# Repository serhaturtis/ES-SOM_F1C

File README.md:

<div id="top"></div>

<br />
<div align="center">

<h3 align="center">SOM-F1C</h3>

  <p align="center">
    A System-on-Module With Allwinner F1C Processor 
  </p>
</div>

<!-- WHAT -->
## What?

This is a linux capable system-on-module board made with Allwinner F1C processor. It can hold SPI flash memory (like 16MB NOR or 128MB NAND) on board. 

## Why?

Because I wanted to.

## How?

Headers are placed to the egdes so that manufacturer can recognize it for edge plating.

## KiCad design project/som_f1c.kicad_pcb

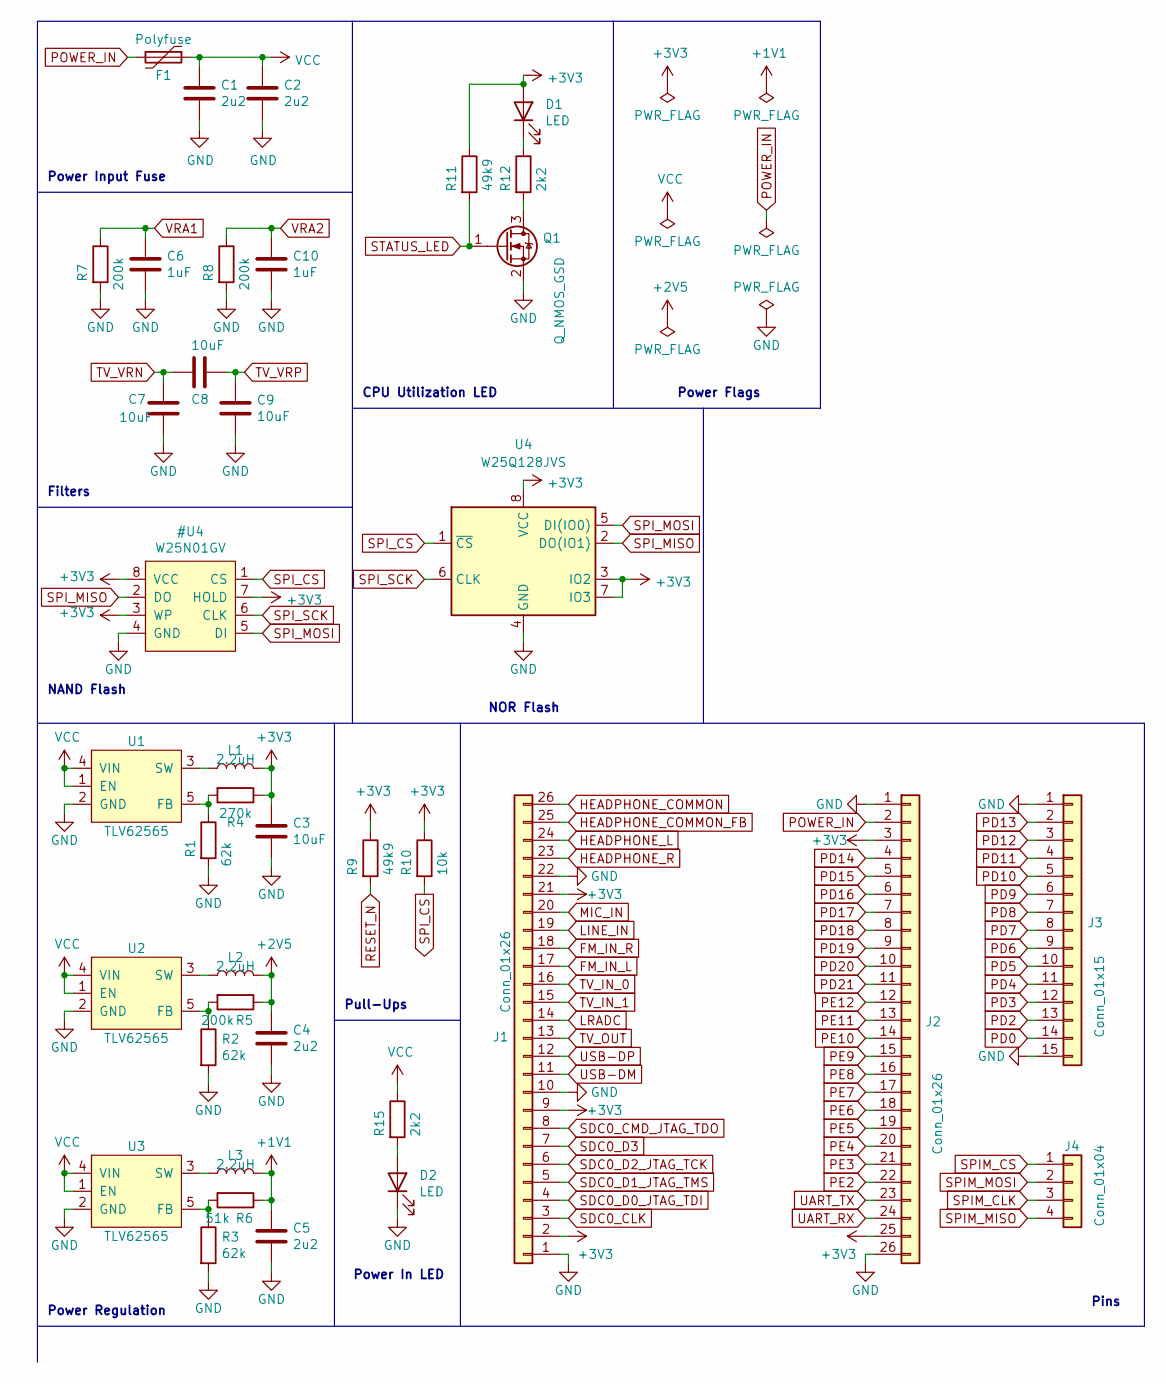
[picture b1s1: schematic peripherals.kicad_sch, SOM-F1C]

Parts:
C1, C2, C4, C5: 2u2; C_0402_1005Metric
C3, C7, C8, C9: 10uF; C_0402_1005Metric
C6, C10: 1uF; C_0402_1005Metric
D1, D2: LED; LED_0402_1005Metric
F1: Polyfuse; Fuse_1206_3216Metric
J1, J2: Conn_01x26; PinHeader_1x26_P1.27mm_Vertical
J3: Conn_01x15; PinHeader_1x15_P1.27mm_Vertical
J4: Conn_01x04; PinHeader_1x04_P1.27mm_Vertical
L1, L2, L3: 2.2uH; L_0805_2012Metric
Q1: Q_NMOS_GSD; SOT-323_SC-70
R1, R2, R3: 62k; R_0402_1005Metric
R4: 270k; R_0402_1005Metric
R5, R7, R8: 200k; R_0402_1005Metric
R6: 51k; R_0402_1005Metric
R9, R11: 49k9; R_0402_1005Metric
R10: 10k; R_0402_1005Metric
R12, R15: 2k2; R_0402_1005Metric
U1, U2, U3: TLV62565; SOT-23-5
U4: W25Q128JVS; SOIC-8_5.23x5.23mm_P1.27mm

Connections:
+1V1: C5.1, L3.2, R6.1; also elsewhere on the board
+2V5: C4.1, L2.2, R5.1; also elsewhere on the board
FM_IN_L: J1.17; also elsewhere on the board
FM_IN_R: J1.18; also elsewhere on the board
HEADPHONE_COMMON: J1.26; also elsewhere on the board
HEADPHONE_COMMON_FB: J1.25; also elsewhere on the board
HEADPHONE_L: J1.24; also elsewhere on the board
HEADPHONE_R: J1.23; also elsewhere on the board
LINE_IN: J1.19; also elsewhere on the board
LRADC: J1.14; also elsewhere on the board
MIC_IN: J1.20; also elsewhere on the board
unnamed: D1.1 (K), R12.1
unnamed: D2.2 (A), R15.2
unnamed: L1.1, U1.3 (SW)
unnamed: L2.1, U2.3 (SW)
unnamed: L3.1, U3.3 (SW)
unnamed: Q1.3 (D), R12.2
unnamed: R1.1, R4.2, U1.5 (FB)
unnamed: R2.1, R5.2, U2.5 (FB)
unnamed: R3.1, R6.2, U3.5 (FB)
PD0: J3.14; also elsewhere on the board
PD2: J3.13; also elsewhere on the board
PD3: J3.12; also elsewhere on the board
PD4: J3.11; also elsewhere on the board
PD5: J3.10; also elsewhere on the board
PD6: J3.9; also elsewhere on the board
PD7: J3.8; also elsewhere on the board
PD8: J3.7; also elsewhere on the board
PD9: J3.6; also elsewhere on the board
PD10: J3.5; also elsewhere on the board
PD11: J3.4; also elsewhere on the board
PD12: J3.3; also elsewhere on the board
PD13: J3.2; also elsewhere on the board
PD14: J2.4; also elsewhere on the board
PD15: J2.5; also elsewhere on the board
PD16: J2.6; also elsewhere on the board
PD17: J2.7; also elsewhere on the board
PD18: J2.8; also elsewhere on the board
PD19: J2.9; also elsewhere on the board
PD20: J2.10; also elsewhere on the board
PD21: J2.11; also elsewhere on the board
PE2: J2.22; also elsewhere on the board
PE3: J2.21; also elsewhere on the board
PE4: J2.20; also elsewhere on the board
PE5: J2.19; also elsewhere on the board
PE6: J2.18; also elsewhere on the board
PE7: J2.17; also elsewhere on the board
PE8: J2.16; also elsewhere on the board
PE9: J2.15; also elsewhere on the board
PE10: J2.14; also elsewhere on the board
PE11: J2.13; also elsewhere on the board
PE12: J2.12; also elsewhere on the board
POWER_IN: F1.2, J2.2
RESET_N: R9.2; also elsewhere on the board
SDC0_CLK: J1.3; also elsewhere on the board
SDC0_CMD_JTAG_TDO: J1.8; also elsewhere on the board
SDC0_D0_JTAG_TDI: J1.4; also elsewhere on the board
SDC0_D1_JTAG_TMS: J1.5; also elsewhere on the board
SDC0_D2_JTAG_TCK: J1.6; also elsewhere on the board
SDC0_D3: J1.7; also elsewhere on the board
SPIM_CLK: J4.3; also elsewhere on the board
SPIM_CS: J4.1; also elsewhere on the board
SPIM_MISO: J4.4; also elsewhere on the board
SPIM_MOSI: J4.2; also elsewhere on the board
STATUS_LED: Q1.1 (G), R11.2; also elsewhere on the board
TV_IN_0: J1.16; also elsewhere on the board
TV_IN_1: J1.15; also elsewhere on the board
TV_OUT: J1.13; also elsewhere on the board
TV_VRN: C7.1, C8.2; also elsewhere on the board
TV_VRP: C8.1, C9.1; also elsewhere on the board
UART_RX: J2.24; also elsewhere on the board
UART_TX: J2.23; also elsewhere on the board
USB-DM: J1.11; also elsewhere on the board
USB-DP: J1.12; also elsewhere on the board
VCC: C1.1, C2.1, F1.1, R15.1, U1.1 (EN), U1.4 (VIN), U2.1 (EN), U2.4 (VIN), U3.1 (EN), U3.4 (VIN)
VRA1: C6.1, R7.1; also elsewhere on the board
VRA2: C10.1, R8.1; also elsewhere on the board

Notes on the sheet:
NOR Flash
Pull-Ups
CPU Utilization LED
Power Regulation
Power Flags
NAND Flash
Pins
Power Input Fuse
Filters
Power In LED

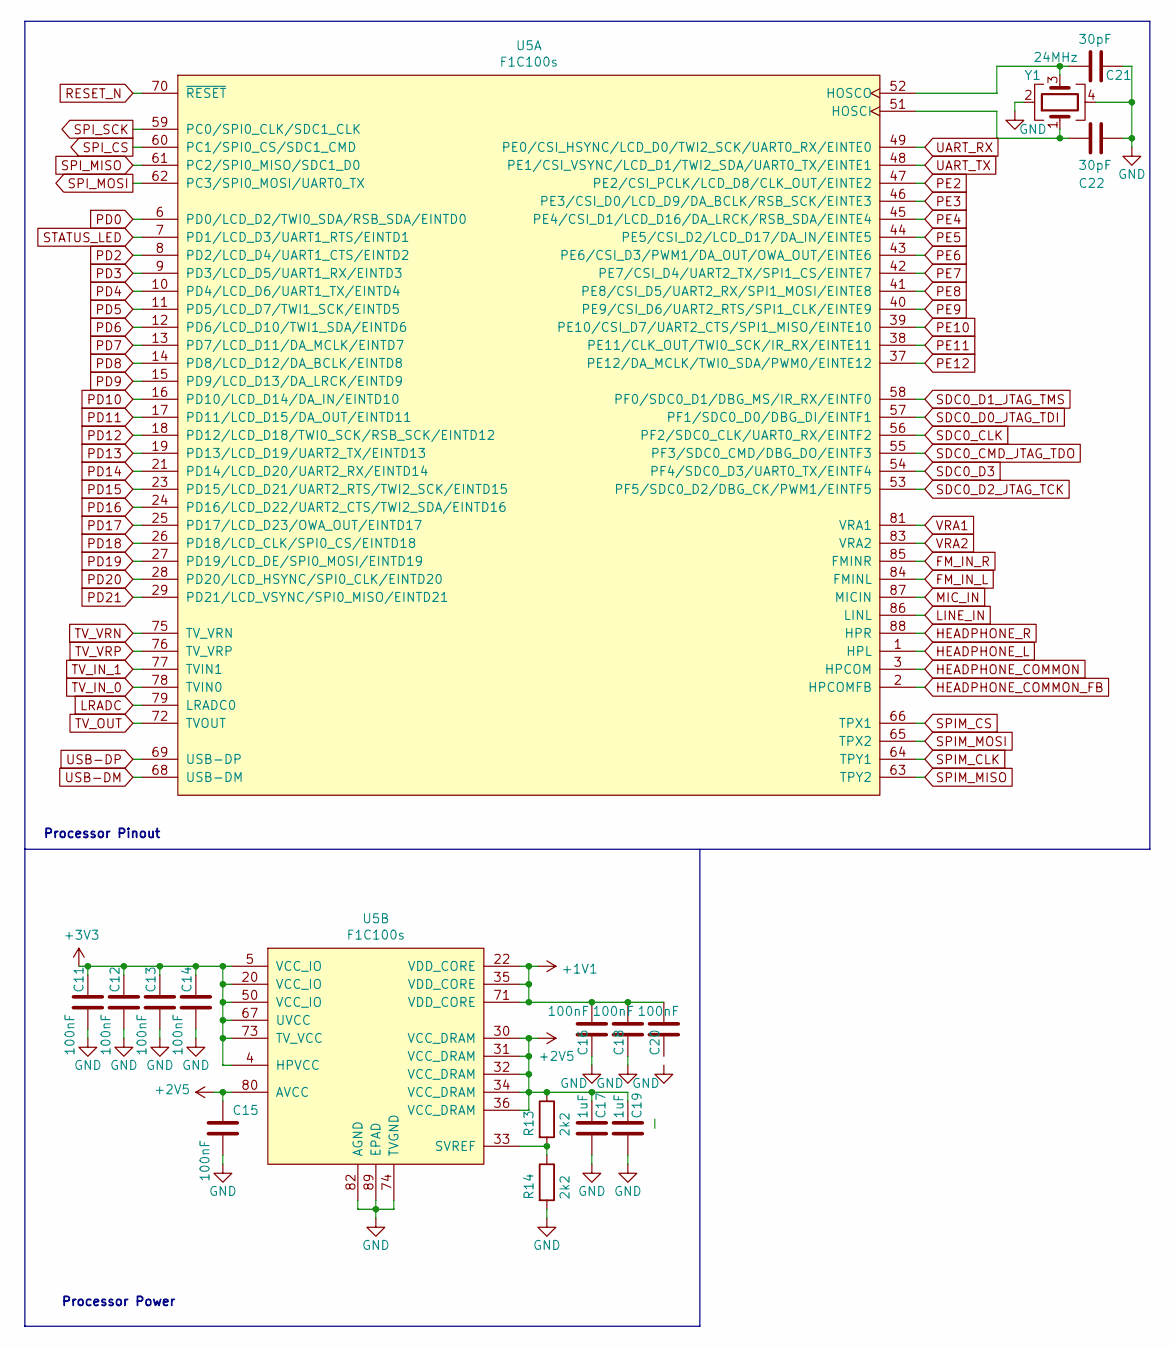
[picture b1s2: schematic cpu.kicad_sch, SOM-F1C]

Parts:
C11, C12, C13, C14, C15, C16, C18, C20: 100nF; C_0402_1005Metric
C17, C19: 1uF; C_0402_1005Metric
C21, C22: 30pF; C_0402_1005Metric
R13, R14: 2k2; R_0402_1005Metric
U5: F1C100s; QFN-88_EP_10x10_Pitch0.4mm
Y1: 24MHz; Crystal_SMD_2016-4Pin_2.0x1.6mm

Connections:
+1V1: C16.1, C18.1, C20.1, U5.22 (VDD_CORE), U5.35 (VDD_CORE), U5.71 (VDD_CORE); also elsewhere on the board
+2V5: C15.1, C17.1, C19.1, R13.1, U5.30 (VCC_DRAM), U5.31 (VCC_DRAM), U5.32 (VCC_DRAM), U5.34 (VCC_DRAM), U5.36 (VCC_DRAM), U5.80 (AVCC); also elsewhere on the board
FM_IN_L: U5.84 (FMINL); also elsewhere on the board
FM_IN_R: U5.85 (FMINR); also elsewhere on the board
HEADPHONE_COMMON: U5.3 (HPCOM); also elsewhere on the board
HEADPHONE_COMMON_FB: U5.2 (HPCOMFB); also elsewhere on the board
HEADPHONE_L: U5.1 (HPL); also elsewhere on the board
HEADPHONE_R: U5.88 (HPR); also elsewhere on the board
LINE_IN: U5.86 (LINL); also elsewhere on the board
LRADC: U5.79 (LRADC0); also elsewhere on the board
MIC_IN: U5.87 (MICIN); also elsewhere on the board
unnamed: C21.2, U5.52 (HOSCO), Y1.3
unnamed: C22.2, U5.51 (HOSCI), Y1.1
unnamed: R13.2, R14.1, U5.33 (SVREF)
PD0: U5.6 (PD0/LCD_D2/TWI0_SDA/RSB_SDA/EINTD0); also elsewhere on the board
PD2: U5.8 (PD2/LCD_D4/UART1_CTS/EINTD2); also elsewhere on the board
PD3: U5.9 (PD3/LCD_D5/UART1_RX/EINTD3); also elsewhere on the board
PD4: U5.10 (PD4/LCD_D6/UART1_TX/EINTD4); also elsewhere on the board
PD5: U5.11 (PD5/LCD_D7/TWI1_SCK/EINTD5); also elsewhere on the board
PD6: U5.12 (PD6/LCD_D10/TWI1_SDA/EINTD6); also elsewhere on the board
PD7: U5.13 (PD7/LCD_D11/DA_MCLK/EINTD7); also elsewhere on the board
PD8: U5.14 (PD8/LCD_D12/DA_BCLK/EINTD8); also elsewhere on the board
PD9: U5.15 (PD9/LCD_D13/DA_LRCK/EINTD9); also elsewhere on the board
PD10: U5.16 (PD10/LCD_D14/DA_IN/EINTD10); also elsewhere on the board
PD11: U5.17 (PD11/LCD_D15/DA_OUT/EINTD11); also elsewhere on the board
PD12: U5.18 (PD12/LCD_D18/TWI0_SCK/RSB_SCK/EINTD12); also elsewhere on the board
PD13: U5.19 (PD13/LCD_D19/UART2_TX/EINTD13); also elsewhere on the board
PD14: U5.21 (PD14/LCD_D20/UART2_RX/EINTD14); also elsewhere on the board
PD15: U5.23 (PD15/LCD_D21/UART2_RTS/TWI2_SCK/EINTD15); also elsewhere on the board
PD16: U5.24 (PD16/LCD_D22/UART2_CTS/TWI2_SDA/EINTD16); also elsewhere on the board
PD17: U5.25 (PD17/LCD_D23/OWA_OUT/EINTD17); also elsewhere on the board
PD18: U5.26 (PD18/LCD_CLK/SPI0_CS/EINTD18); also elsewhere on the board
PD19: U5.27 (PD19/LCD_DE/SPI0_MOSI/EINTD19); also elsewhere on the board
PD20: U5.28 (PD20/LCD_HSYNC/SPI0_CLK/EINTD20); also elsewhere on the board
PD21: U5.29 (PD21/LCD_VSYNC/SPI0_MISO/EINTD21); also elsewhere on the board
PE2: U5.47 (PE2/CSI_PCLK/LCD_D8/CLK_OUT/EINTE2); also elsewhere on the board
PE3: U5.46 (PE3/CSI_D0/LCD_D9/DA_BCLK/RSB_SCK/EINTE3); also elsewhere on the board
PE4: U5.45 (PE4/CSI_D1/LCD_D16/DA_LRCK/RSB_SDA/EINT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); also elsewhere on the board
PE5: U5.44 (PE5/CSI_D2/LCD_D17/DA_IN/EINTE5); also elsewhere on the board
PE6: U5.43 (PE6/CSI_D3/PWM1/DA_OUT/OWA_OUT/EINTE6); also elsewhere on the board
PE7: U5.42 (PE7/CSI_D4/UART2_TX/SPI1_CS/EINTE7); also elsewhere on the board
PE8: U5.41 (PE8/CSI_D5/UART2_RX/SPI1_MOSI/EINTE8); also elsewhere on the board
PE9: U5.40 (PE9/CSI_D6/UART2_RTS/SPI1_CLK/EINTE9); also elsewhere on the board
PE10: U5.39 (PE10/CSI_D7/UART2_CTS/SPI1_MISO/EINTE10); also elsewhere on the board
PE11: U5.38 (PE11/CLK_OUT/TWI0_SCK/IR_RX/EINTE11); also elsewhere on the board
PE12: U5.37 (PE12/DA_MCLK/TWI0_SDA/PWM0/EINTE12); also elsewhere on the board
RESET_N: U5.70 (~RESET); also elsewhere on the board
SDC0_CLK: U5.56 (PF2/SDC0_CLK/UART0_RX/EINTF2); also elsewhere on the board
SDC0_CMD_JTAG_TDO: U5.55 (PF3/SDC0_CMD/DBG_DO/EINTF3); also elsewhere on the board
SDC0_D0_JTAG_TDI: U5.57 (PF1/SDC0_D0/DBG_DI/EINTF1); also elsewhere on the board
SDC0_D1_JTAG_TMS: U5.58 (PF0/SDC0_D1/DBG_MS/IR_RX/EINTF0); also elsewhere on the board
SDC0_D2_JTAG_TCK: U5.53 (PF5/SDC0_D2/DBG_CK/PWM1/EINTF5); also elsewhere on the board
SDC0_D3: U5.54 (PF4/SDC0_D3/UART0_TX/EINTF4); also elsewhere on the board
SPIM_CLK: U5.64 (TPY1); also elsewhere on the board
SPIM_CS: U5.66 (TPX1); also elsewhere on the board
SPIM_MISO: U5.63 (TPY2); also elsewhere on the board
SPIM_MOSI: U5.65 (TPX2); also elsewhere on the board
STATUS_LED: U5.7 (PD1/LCD_D3/UART1_RTS/EINTD1); also elsewhere on the board
TV_IN_0: U5.78 (TVIN0); also elsewhere on the board
TV_IN_1: U5.77 (TVIN1); also elsewhere on the board
TV_OUT: U5.72 (TVOUT); also elsewhere on the board
TV_VRN: U5.75 (TV_VRN); also elsewhere on the board
TV_VRP: U5.76 (TV_VRP); also elsewhere on the board
UART_RX: U5.49 (PE0/CSI_HSYNC/LCD_D0/TWI2_SCK/UART0_RX/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); also elsewhere on the board
UART_TX: U5.48 (PE1/CSI_VSYNC/LCD_D1/TWI2_SDA/UART0_TX/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); also elsewhere on the board
USB-DM: U5.68 (USB-DM); also elsewhere on the board
USB-DP: U5.69 (USB-DP); also elsewhere on the board
VRA1: U5.81 (VRA1); also elsewhere on the board
VRA2: U5.83 (VRA2); also elsewhere on the board

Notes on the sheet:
Processor Power
Processor Pinout

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
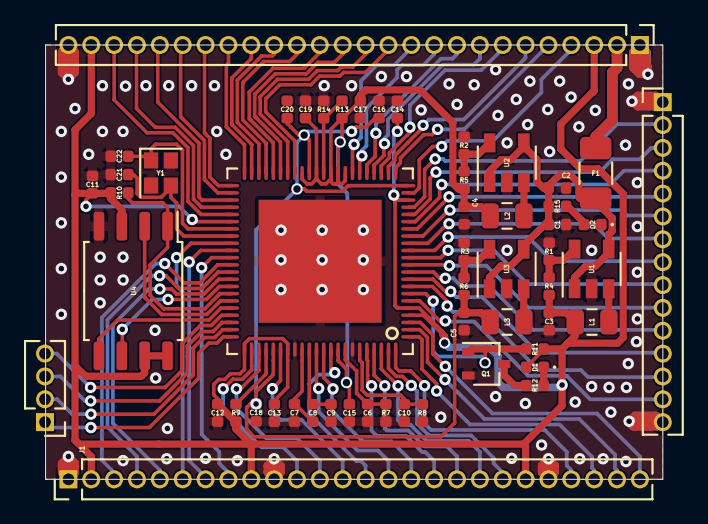
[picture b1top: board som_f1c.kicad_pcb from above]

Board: 2 copper layers, 34.3 x 24.1 mm, 54 parts (0 on the bottom side), 86 nets.

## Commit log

2022-01-09 Initial commit.
2023-01-08 updated to version 6.x
2023-01-08 fixed some drc errors, added module footprint and symbol library
2023-03-27 added extra spi pins
2023-03-27 removes bups
